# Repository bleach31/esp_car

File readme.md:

View this project on [CADLAB.io](https://cadlab.io/project/1962). 

### diff drive car by esp-wroom-32

Cuddling Alexa
### software
esp32、androidはソースコードの中

microbit:https://makecode.microbit.org/_AAq7xpe3sfrz

### hardware

モータマウント：https://www.thingiverse.com/thing:1364768
↑の12mmのやつ。

#### parts memo
- 100kオーム 1608 http://akizukidenshi.com/catalog/g/gR-11792/
- 5v 1a 縦型　 http://akizukidenshi.com/catalog/g/gI-00537/
    http://akizukidenshi.com/catalog/g/gM-13536/
    発熱がひどかったのでこっちに変更。6.5vから使えて最大1A、効率90-94%

    3.3V系統もBLEを使うと結構やばい。
    http://akizukidenshi.com/catalog/g/gM-13535/で設計すればよかった。
    
    回路設計時は入手性がよくてリポ2セル(最低6.4v)で動くスイッチングレギュレータ見つけられなかった・・・。

- 電源用mosfet http://akizukidenshi.com/catalog/g/gI-03942/
- 47uF http://akizukidenshi.com/catalog/g/gP-04657/
- 100uF http://akizukidenshi.com/catalog/g/gP-08290/
- モータードライバ　http://akizukidenshi.com/catalog/g/gI-11317/
- 3.3V 1.5A http://akizukidenshi.com/catalog/g/gI-02558/
- mos http://akizukidenshi.com/catalog/g/gI-01233/
- タクトスイッチ：http://akizukidenshi.com/catalog/g/gP-06185/
- モータコネクタzh 6pin　ｘ2：https://www.sengoku.co.jp/mod/sgk_cart/detail.php?code=4A44-P4HR
- リポ　2セル　3.7*2=7.4(6.4v-8.4v)　46ｘ20x 18未満
- LEDフルカラー4つ http://akizukidenshi.com/catalog/g/gI-07915/
- 電源コネクタ 　jstコネクタのメス
- ５Vアウトコネクタ　jstコネクタのメス　https://www.amazon.co.jp/SODIAL-R-10ペアの150mm-JSTコネクタープラグケーブルライン-オス＋メス-RC-BECリポ電池の為/dp/B00O2MPSU4/ref=sr_1_9?ie=UTF8&qid=1531495570&sr=8-9&keywords=jst
- 電源スイッチ, 横向き　http://akizukidenshi.com/catalog/g/gP-08789/
- ブザー http://akizukidenshi.com/catalog/g/gP-04497/
- アレクサ給電用microUSB:　http://www.epanorama.net/newepa/2016/04/27/qi-receiver-teardown/
- モータマウント m2 5mmぐらい4個　, M3　ネジ＋ナット　5㎜ぐらい ４個
- 距離センサ GY-530 3つ　4pin。10.5x13.3 https://www.smart-prototyping.com/VL53L0X-Time-of-Flight-Distance-Sensor-GY-530
- 9軸+気温+気圧　GY-91 (MPU9250+BMP280) 6pin　14.3mm * 20.5mm　https://electronics.semaf.at/9DOF-Axis-IMU-MPU9250-and-BMP280-Atmospheric-Sensor

1608の抵抗10k,20kとか
1608のコンデンサ0.1uF 10uFとか。

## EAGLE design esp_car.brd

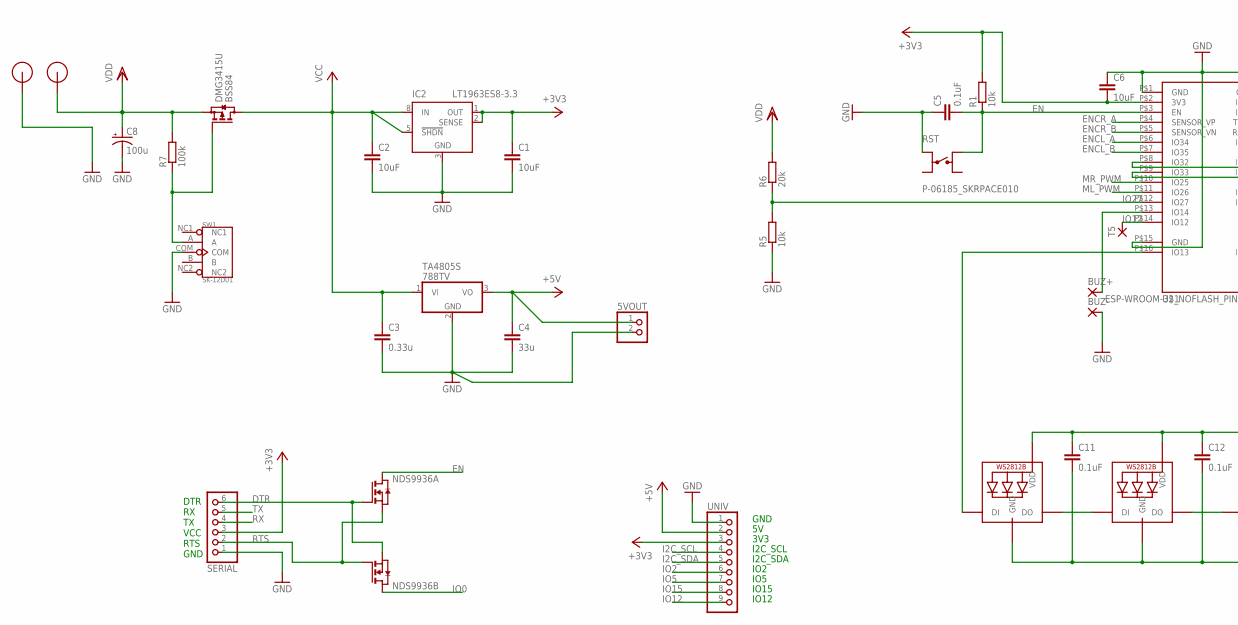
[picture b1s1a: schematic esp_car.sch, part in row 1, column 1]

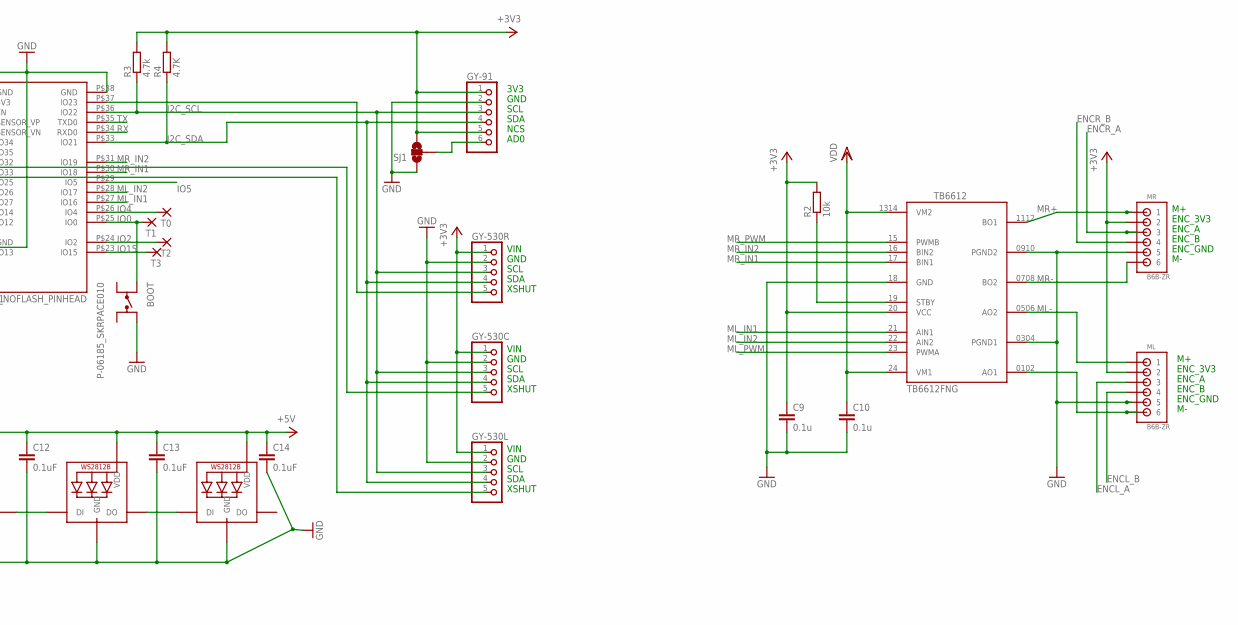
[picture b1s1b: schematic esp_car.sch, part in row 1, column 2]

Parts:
5VOUT: PINHD-1X2; 1X02
BOOT: P-06185_SKRPACE010; SKRP
BUZ+: SMD2; SMD1,27-2,54
BUZ-: SMD2; SMD1,27-2,54
C1, C2, C6: 10uF; C1608
C3: 0.33u; C1608
C4: 33u; C3225
C5, C11, C12, C13, C14: 0.1uF; C1608
C8: 100u; E2,5-6
C9, C10: 0.1u; C1608
DMG3415U: BSS84; SOT23
GY-91: PINHD-1X6; 1X06
GY-530C, GY-530L, GY-530R: PINHD-1X5; 1X05
IC2: LT1963ES8-3.3; SOIC8
LED_FL: WS2812B5050; WS2812B
LED_FR: WS2812B5050; WS2812B
LED_RL: WS2812B5050; WS2812B
LED_RR: WS2812B5050; WS2812B
ML: B6B-ZR
MR: B6B-ZR
NDS9936: NMOS2SO8; SO8
R1, R2, R5: 10k; R0603
R3: 4.7k; R0603
R4: 4.7K; R0603
R6: 20k; R0603
R7: 100k; R0603
RST: P-06185_SKRPACE010; SKRP
SERIAL: PINHD-1X6; 1X06
SJ1: SOLDERJUMPER_2WAYS; SJ_3
SW1: SK-12D01; SW5-2.0-8.8X4.4X4.7MM-90D
T0, T1, T2, T3, T5: SMD5; SMD2,54-5,08
TA4805S: 788TV; TO220V
TB6612: TB6612_NEW; SSOP24_TB6612
U$1: ESP-WROOM-32_NOFLASH_PINHEAD
U$5, U$7: 2.0
UNIV: PINHD-1X9; 1X09-BIG

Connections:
+3V3: C1.1, C6.2, C9.1, GY-91.1, GY-91.5, GY-530C.1, GY-530L.1, GY-530R.1, IC2.1 (OUT), IC2.2 (SENSE), ML.2, MR.2, R1.2, R2.2, R3.2, R4.2, SERIAL.3, SJ1.3, TB6612.20 (VCC), U$1.P$2 (3V3), UNIV.3
+5V: 5VOUT.1, C4.1, C11.1, C12.1, C13.1, C14.1, LED_FL.1-VDD (VDD), LED_FR.1-VDD (VDD), LED_RL.1-VDD (VDD), LED_RR.1-VDD (VDD), TA4805S.3 (VO), UNIV.2
DTR: NDS9936.2 (G), NDS9936.3 (S), SERIAL.6
EN: C5.2, NDS9936.7 (D), NDS9936.8 (D), R1.1, RST.2A, U$1.P$3 (EN)
ENCL_A: ML.3, U$1.P$6 (IO34)
ENCL_B: ML.4, U$1.P$7 (IO35)
ENCR_A: MR.3, U$1.P$4 (SENSOR_VP)
ENCR_B: MR.4, U$1.P$5 (SENSOR_VN)
GND: 5VOUT.2, BOOT.2A, BUZ-.1, C1.2, C2.2, C3.2, C4.2, C5.1, C6.1, C8.-, C9.2, C10.2, C11.2, C12.2, C13.2, C14.2, GY-91.2, GY-530C.2, GY-530L.2, GY-530R.2, IC2.3 (GND), IC2.6 (GND), IC2.7 (GND), LED_FL.3-GND (GND), LED_FR.3-GND (GND), LED_RL.3-GND (GND), LED_RR.3-GND (GND), ML.5, MR.5, R5.1, RST.1A, SERIAL.1, SJ1.1, SW1.COM, TA4805S.2 (GND), TB6612.18 (GND), TB6612.0304 (PGND1), TB6612.0910 (PGND2), U$1.P$1 (GND), U$1.P$15 (GND), U$1.P$38 (GND), U$5.P$1, UNIV.1
I2C_SCL: GY-91.3, GY-530C.3, GY-530L.3, GY-530R.3, R3.1, U$1.P$36 (IO22), UNIV.4
I2C_SDA: GY-91.4, GY-530C.4, GY-530L.4, GY-530R.4, R4.1, U$1.P$33 (IO21), UNIV.5
IO0: BOOT.1A, NDS9936.5 (D), NDS9936.6 (D), T1.1, U$1.P$25 (IO0)
IO2: T2.1, U$1.P$24 (IO2), UNIV.6
IO4: T0.1, U$1.P$26 (IO4)
IO5: U$1.P$29 (IO5), UNIV.7
IO12: T5.1, U$1.P$14 (IO12), UNIV.9
IO15: T3.1, U$1.P$23 (IO15), UNIV.8
IO27: R5.2, R6.1, U$1.P$12 (IO27)
ML-: ML.6, TB6612.0102 (AO1)
ML_IN1: TB6612.21 (AIN1), U$1.P$27 (IO16)
ML_IN2: TB6612.22 (AIN2), U$1.P$28 (IO17)
ML_PWM: TB6612.23 (PWMA), U$1.P$11 (IO26)
MR+: MR.1, TB6612.1112 (BO1)
MR-: MR.6, TB6612.0708 (BO2)
MR_IN1: TB6612.17 (BIN1), U$1.P$30 (IO18)
MR_IN2: TB6612.16 (BIN2), U$1.P$31 (IO19)
MR_PWM: TB6612.15 (PWMB), U$1.P$10 (IO25)
unnamed: GY-530C.5, U$1.P$8 (IO32)
unnamed: GY-91.6, SJ1.2
unnamed: GY-530R.5, U$1.P$37 (IO23)
unnamed: LED_FL.2-DOUT (DO), LED_RL.4-DIN (DI)
unnamed: R2.1, TB6612.19 (STBY)
unnamed: BUZ+.1, U$1.P$13 (IO14)
unnamed: LED_RL.2-DOUT (DO), LED_RR.4-DIN (DI)
unnamed: LED_FR.4-DIN (DI), LED_RR.2-DOUT (DO)
unnamed: LED_FL.4-DIN (DI), U$1.P$16 (IO13)
unnamed: GY-530L.5, U$1.P$9 (IO33)
unnamed: ML.1, TB6612.0506 (AO2)
unnamed: DMG3415U.1 (G), R7.1, SW1.A
RTS: NDS9936.1 (S), NDS9936.4 (G), SERIAL.2
RX: SERIAL.4, U$1.P$34 (RXD0)
TX: SERIAL.5, U$1.P$35 (TXD0)
VCC: C2.1, C3.1, DMG3415U.3 (D), IC2.5 (!SHDN), IC2.8 (IN), TA4805S.1 (VI)
VDD: C8.+, C10.1, DMG3415U.2 (S), R6.2, R7.2, TB6612.24 (VM1), TB6612.1314 (VM2), U$7.P$1

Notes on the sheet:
DTR RX TX VCC RTS GND
ENC_3V3
ENC_A
ENC_B
ENC_GND
3V3
GND
SCL
SDA
NCS
AD0
VIN
XSHUT
I2C_SCL
I2C_SDA
IO2
IO5
IO15
IO12

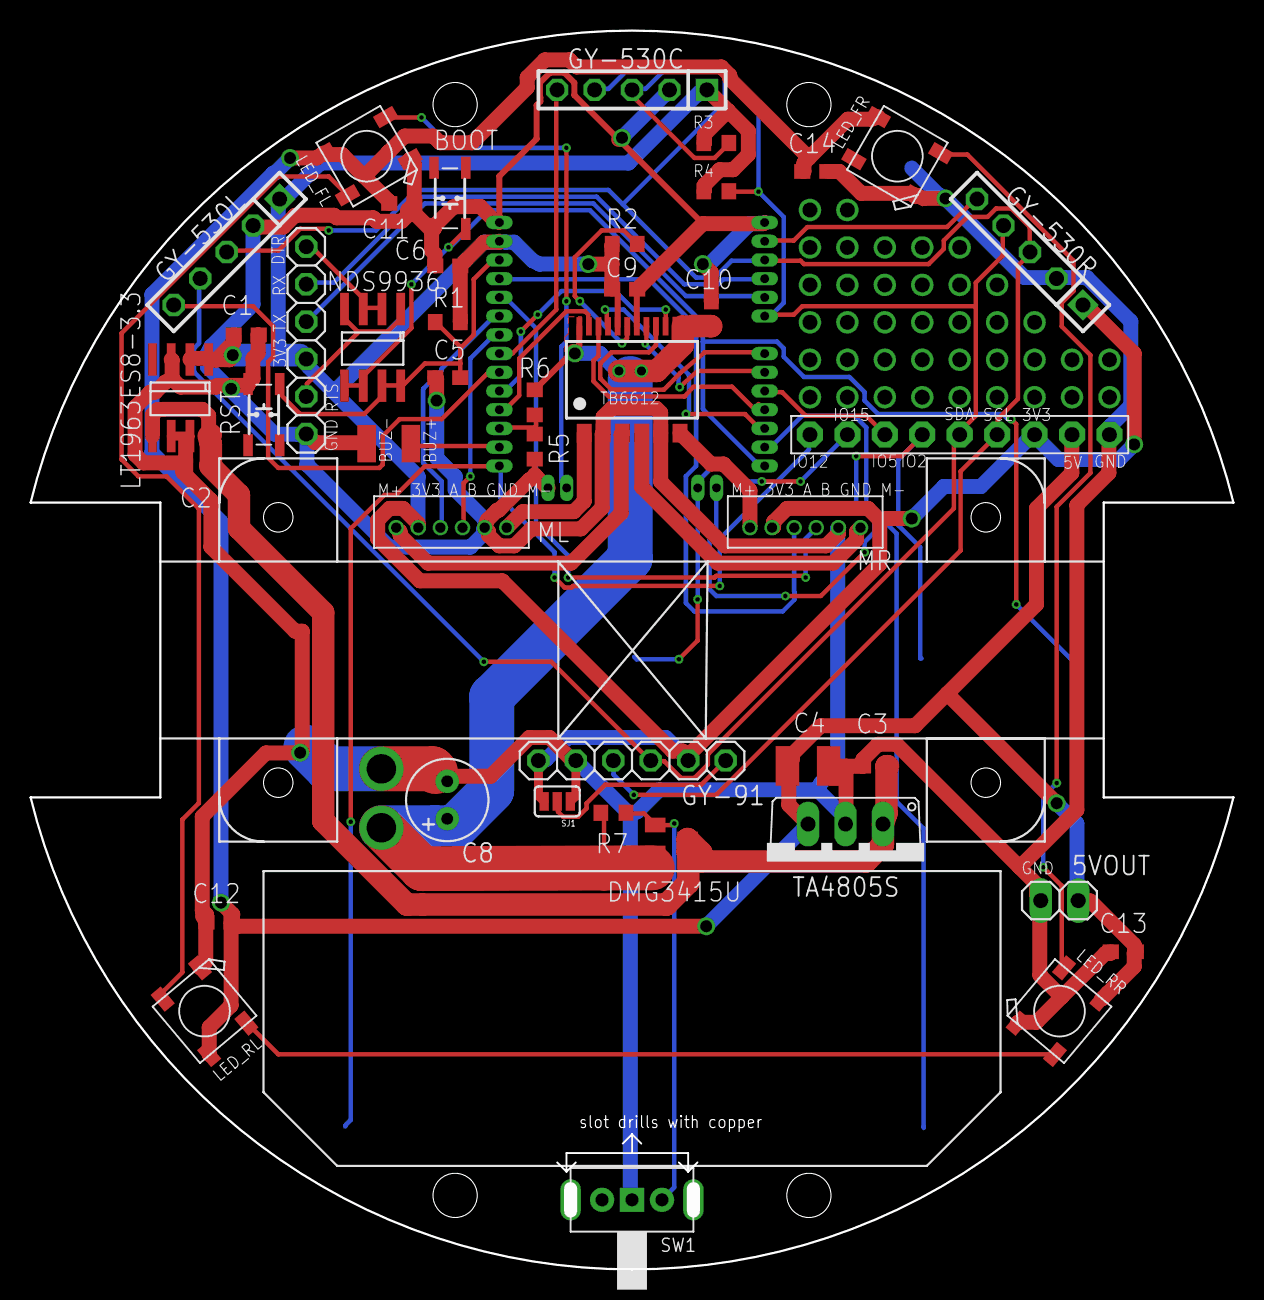
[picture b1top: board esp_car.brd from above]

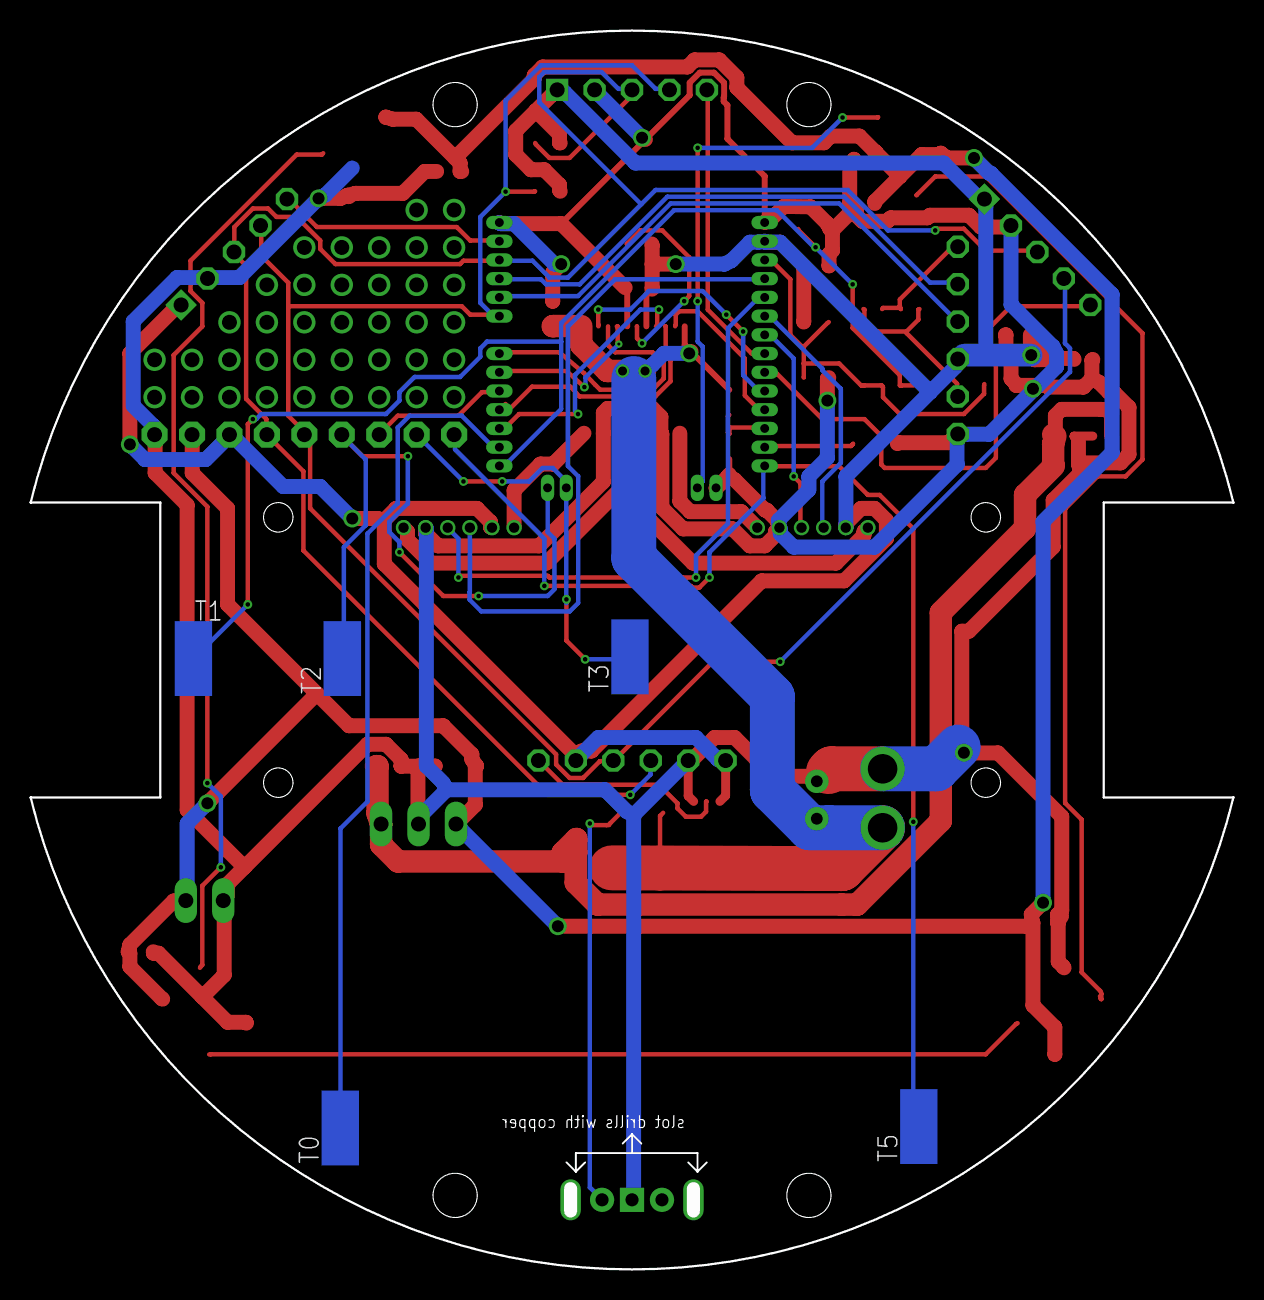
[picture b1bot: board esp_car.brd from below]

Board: 2 copper layers, 80.9 x 83.3 mm, 52 parts (5 on the bottom side), 44 nets.

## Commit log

2018-06-05 project add
2018-06-06 daliy commit
2018-06-10 chematic v1.0
2018-06-10 board test
2018-06-13 sche fix,board test
2018-06-13 pdf add
2018-06-15 from office
2018-06-17 daily
2018-06-18 art work
2018-06-19 ユニバーサル部分追加、NETCLASS調整
2018-06-19 配線良し
2018-06-19 wire 100% 初版
2018-06-20 5vレギュレータをLDOに変更、配線100% v2
2018-06-20 電源用MOSFET追加、VDD見直し
2018-06-20 airwireなし
2018-06-21 esp32のviaの径設定ミス修正、NMOS向き修正、配線やり直し完了
2018-06-21 PDF,ガーバー出力
2018-06-21 GNDを太く。サーマルランドが細かった
2018-06-21 コンデンサの向きを修正
2018-06-22 c1,c9,r2,r3,r4 微修正 nmos向き修正、so8シルク追加
2018-06-22 基板FIX、発注
2018-06-22 remove old pdf
2018-06-23 add board pdf
2018-07-08 code add
2018-07-13 add mecha
2018-07-13 tof sensor
2018-07-13 add parts memo
2018-07-14 touch read
2018-07-16 抵抗値の修正
2018-07-16 BLEテスト
2018-07-16 探索実装
2018-07-17 sarch object
2018-07-17 とりあえず。
2018-07-17 add ignore
2018-07-17 led space
2018-07-17 接合部の付け根を太く
2018-07-22 qeiテスト
2018-07-22 速度制御
2018-07-22 BLEをいろいろおためし
2018-07-22 パーツ変更
2018-07-22 コメント修正
2018-07-24 ble mode
2018-07-24 バッテリーポート変更、BLEのモジュールを適当に配置
2018-07-25 ble rx parser
2018-07-25 BLEラジコン実装
2018-07-26 RCの感度変更
2018-07-28 ubit
2018-07-28 ubit ok
2018-07-28 instractuions in case(switch) needs {} ... why?
2018-07-28 ubit ble uart mode (not yet text parser)
2018-07-30 parser
2018-07-30 ubit 連携OK
2018-07-31 demo mode
2018-08-02 制御ゲインを微調整。無駄ソース削除、リードミー修正
2019-07-05 Backlink to CADLAB.io has been added.
2020-10-14 add flier

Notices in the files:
parts and their libraries:
SparkFun: Licensing: CC v3.0 Share-Alike You are welcome to use this library for commercial purposes.
esp32 _my: Creative Commons Attribution-ShareAlike 4.0 International
